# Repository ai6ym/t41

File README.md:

# T41-EP SDT Project Files

Hardware and software files for the T41-EP SDT as sold / distributed by [AI6YM](https://ai6ym.radio/t41-ep-sdt). These files are branched from [K9HZ's Repo](https://github.com/DRWJSCHMIDT/T41) and [G0ORX's Repo](https://github.com/g0orx/T41-EP) with some files from the [SoftwareControlledHamRadio Groups.IO](https://groups.io/g/SoftwareControlledHamRadio).

Changes present here are minor modifications made to enable automated SMD assembly, pre-programming of the Teensy and ATTiny, etc. Refinements to various BOMs (bill of materials) have been made to substitute parts which are unavailable or correct errors.

Software within this repository is licensed under GNU GPL v3. Hardware designs are licensed under TAPR OHL Version 1.0. In addition to these licenses the original creators of the T41, Albert F Peter (AC8GY) and Dr. Jack Purdum (W8TEE), have requested that any commercial use of the designs receive their written permission.

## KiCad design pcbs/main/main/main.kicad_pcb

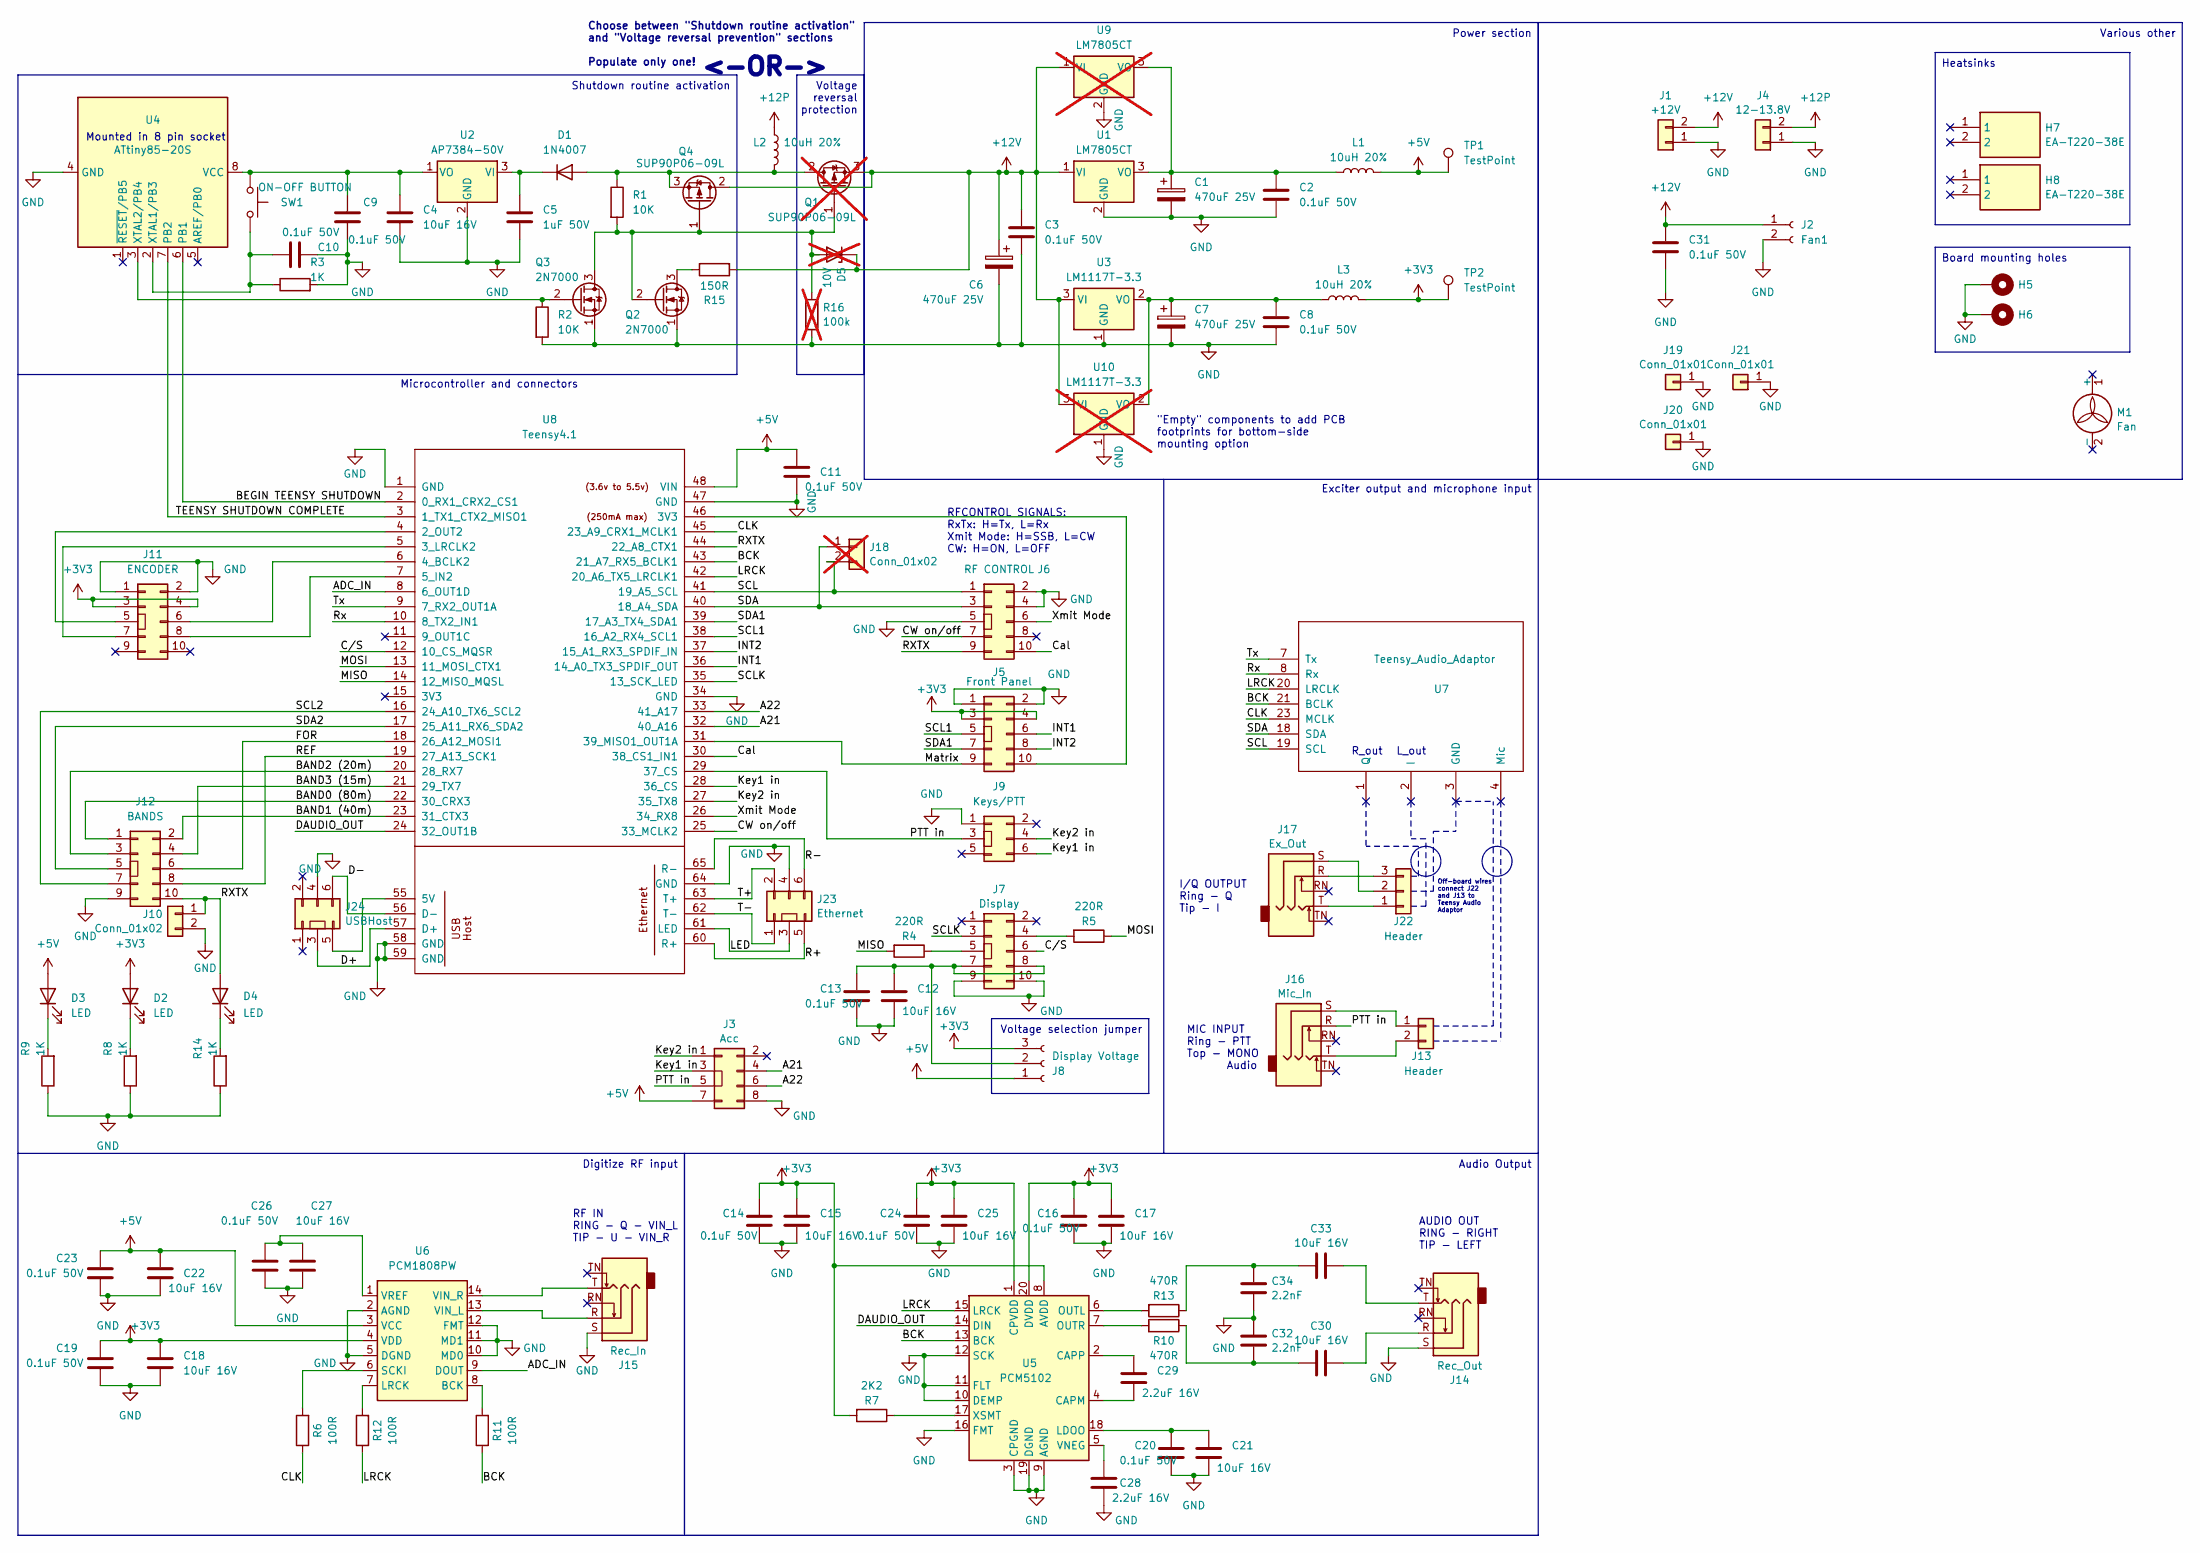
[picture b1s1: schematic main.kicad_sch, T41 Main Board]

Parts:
C1, C6, C7: 470uF 25V; CP_Radial_D10.0mm_P5.00mm; Mouser 667-ECA-1EM471
C2, C3, C8, C9, C10, C11, C13, C14, C16, C19, C20, C23, C24, C26, C31: 0.1uF 50V; C_1206_3216Metric; Mouser C1206C104K5RACTU
C4, C12, C15, C17, C18, C21, C22, C25, C27, C30, C33: 10uF 16V; C_1206_3216Metric; Mouser 80-C1206C106K4P
C5: 1uF 50V; C_1206_3216Metric; Mouser 187-CL31B105KBHNNNE
C28, C29: 2.2uF 16V; C_1206_3216Metric; Mouser 80-C1206C225K5R
C32, C34: 2.2nF; C_1206_3216Metric; Mouser 80-C1206C222K5RAC
D1: 1N4007; D_SMA; Mouser 621-S1A-F
D2, D3, D4: LED; D_1206_3216Metric; Mouser 645-599-0220-007F
D5: 10V; D_SMA; Mouser 78-MMSZ5240C-E3-08; not fitted
H5, H6: MountingHole_4.3mm_M4_DIN965_Pad
H7, H8: EA-T220-38E; EAT22038E; Mouser Part Number 588-EA-T220-38E
J1: +12V; PinHeader_1x02_P5.08mm_Vertical
J2: Fan1; PinHeader_1x02_P2.54mm_Vertical
J3: Acc; IDC-Header_2x04_P2.54mm_Vertical
J4: 12-13.8V; PinHeader_1x02_P5.08mm_Vertical
J5: Front Panel; IDC-Header_2x05_P2.54mm_Vertical
J6: RF CONTROL; IDC-Header_2x05_P2.54mm_Vertical
J7: Display; IDC-Header_2x05_P2.54mm_Vertical
J8: Display Voltage; PinHeader_1x03_P2.54mm_Vertical
J9: Keys/PTT; IDC-Header_2x03_P2.54mm_Vertical
J10: Conn_01x02; PinHeader_1x02_P2.54mm_Vertical
J11: ENCODER; IDC-Header_2x05_P2.54mm_Vertical
J12: BANDS; IDC-Header_2x05_P2.54mm_Vertical
J13: Header; PinHeader_1x02_P2.54mm_Vertical
J14: Rec_Out; Jack_3.5mm_STX-3081_Horizontal; Mouser 490-SJ1-3515N
J15: Rec_In; Jack_3.5mm_STX-3081_Horizontal; Mouser 490-SJ1-3515N
J16: Mic_In; Jack_3.5mm_STX-3081_Horizontal; Mouser 490-SJ1-3515N
J17: Ex_Out; Jack_3.5mm_STX-3081_Horizontal; Mouser 490-SJ1-3515N
J18: Conn_01x02; PinHeader_1x02_P2.54mm_Vertical; not fitted
J19, J20, J21: Conn_01x01; PinHeader_1x01_P2.54mm_Vertical
J22: Header; PinHeader_1x03_P2.54mm_Vertical
J23: Ethernet; IDC-Header_2x03_P2.54mm_Vertical; Mouser 710-61200621621
J24: USBHost; IDC-Header_2x03_P2.54mm_Vertical; Mouser 710-61200621621
L1, L2, L3: 10uH 20%; L_Bourns-SRN6028; Mouser 81-1264EY-100MP3
M1: Fan; Mouser 664-AD0412HXK96XT1
Q1: SUP90P06-09L; TO-220-3_Vertical; not fitted
Q2, Q3: 2N7000; TO-92_Inline; Mouser 512-2N7000BU
Q4: SUP90P06-09L; TO-220-3_Vertical
R1, R2: 10K; R_1206_3216Metric; Mouser CRCW120610K0FKEB
R3, R8, R9, R14: 1K; R_1206_3216Metric; Mouser CRCW12061K00JNEAC
R4, R5: 220R; R_1206_3216Metric; Mouser 279-CRGCQ1206J220R
R6, R11, R12: 100R; R_1206_3216Metric; Mouser 652-CR1206FX-1000ELF
R7: 2K2; R_1206_3216Metric; Mouser CRCW12062K20JNEAC
R10, R13: 470R; R_1206_3216Metric; Mouser CRCW1206470RJNEAC
R15: 150R; R_1206_3216Metric; Mouser 279-CRGCQ1206J150R
R16: 100k; R_1206_3216Metric; Mouser 71-CRCW1206100KFKEB; not fitted
SW1: ON-OFF BUTTON; PinHeader_1x02_P2.54mm_Vertical
TP1, TP2: TestPoint; PinHeader_1x01_P2.54mm_Vertical
U1: LM7805CT; TO-220-3_Vertical; Mouser 926-LM7805CT/NOPB
U2: AP7384-50V; TO-92_Inline_Wide; Mouser AP7381-50V-A
U3: LM1117T-3.3; TO-220-3_Vertical; Mouser 926-LM1117T-3.3/NOPB
U4: ATtiny85-20S; DIP-8_W7.62mm_Socket; Mouser 556-ATTINY85-20PU
U5: PCM5102; TSSOP-20_4.4x6.5mm_P0.65mm; Mouser 595-PCM5102APWR
U6: PCM1808PW; TSSOP-14_4.4x5mm_P0.65mm; Mouser 595-PCM1808PW
U7: Teensy_Audio_Adaptor
U8: Teensy4.1; Teensy41
U9: LM7805CT; TO-220-3_Vertical; Mouser 926-LM7805CT/NOPB; not fitted
U10: LM1117T-3.3; TO-220-3_Vertical; Mouser 926-LM1117T-3.3/NOPB; not fitted

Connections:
+3V3: C14.1, C15.1, C16.1, C17.1, C18.1, C19.1, C24.1, C25.1, D2.2 (A), J5.3, J5.4, J8.3, J11.3, J11.4, L3.2, R7.2, TP2.1, U5.1 (CPVDD), U5.8 (AVDD), U5.20 (DVDD), U6.4 (VDD)
+5V: C11.1, C22.1, C23.1, D3.2 (A), J3.7, J8.1, L1.2, TP1.1, U6.3 (VCC), U8.48 (VIN)
+12P: J4.2, L2.2
+12V: C3.1, C6.1, C31.1, D5.1 (K), J1.2, J2.1, Q1.3 (S), Q4.2 (D), R15.2, U1.1 (VI), U3.3 (VI), U9.1 (VI), U10.3 (VI)
/A21: J3.4, U8.32 (40_A16)
/A22: J3.6, U8.33 (41_A17)
/ADC_IN: U6.9 (DOUT), U8.8 (6_OUT1D)
/BAND0 (80m): J12.1, U8.22 (30_CRX3)
/BAND1 (40m): J12.2, U8.23 (31_CTX3)
/BAND2 (20m): J12.3, U8.20 (28_RX7)
/BAND3 (15m): J12.4, U8.21 (29_TX7)
/BCK: R11.1, U5.13 (BCK), U7.21 (BCLK), U8.43 (21_A7_RX5_BCLK1)
/BEGIN TEENSY SHUTDOWN: U4.6 (PB1), U8.2 (0_RX1_CRX2_CS1)
/CLK: R6.1, U7.23 (MCLK), U8.45 (23_A9_CRX1_MCLK1)
/CW on/off: J6.7, U8.25 (33_MCLK2)
/Cal: J6.10, U8.30 (38_CS1_IN1)
/C/S: J7.6, U8.12 (10_CS_MQSR)
/D+: J24.3, U8.57 (D+)
/D-: J24.6, U8.56 (D-)
/DAUDIO_OUT: U5.14 (DIN), U8.24 (32_OUT1B)
/FOR: J12.6, U8.18 (26_A12_MOSI1)
/INT1: J5.6, U8.36 (14_A0_TX3_SPDIF_OUT)
/INT2: J5.8, U8.37 (15_A1_RX3_SPDIF_IN)
/Key1 in: J3.3, J9.6, U8.28 (36_CS)
/Key2 in: J3.1, J9.4, U8.27 (35_TX8)
/LED: J23.3, U8.61 (LED)
/LRCK: R12.1, U5.15 (LRCK), U7.20 (LRCLK), U8.42 (20_A6_TX5_LRCLK1)
/MISO: R4.2, U8.14 (12_MISO_MQSL)
/MOSI: R5.1, U8.13 (11_MOSI_CTX1)
/Matrix: J5.9, U8.31 (39_MISO1_OUT1A)
/PTT in: J3.5, J9.3, J16.R, U8.29 (37_CS)
/R+: J23.5, U8.60 (R+)
/R-: J23.6, U8.65 (R-)
/REF: J12.8, U8.19 (27_A13_SCK1)
/RXTX: D4.2 (A), J6.9, J10.1, J12.10, U8.44 (22_A8_CTX1)
/Rx: U7.8 (Rx), U8.10 (8_TX2_IN1)
/SCL: J6.1, J18.2, U7.19 (SCL), U8.41 (19_A5_SCL)
/SCL1: J5.5, U8.38 (16_A2_RX4_SCL1)
/SCL2: J12.7, U8.16 (24_A10_TX6_SCL2)
/SCLK: J7.3, U8.35 (13_SCK_LED)
/SDA: J6.3, J18.1, U7.18 (SDA), U8.40 (18_A4_SDA)
/SDA1: J5.7, U8.39 (17_A3_TX4_SDA1)
/SDA2: J12.5, U8.17 (25_A11_RX6_SDA2)
/T+: J23.2, U8.63 (T+)
/T-: J23.1, U8.62 (T-)
/TEENSY SHUTDOWN COMPLETE: U4.7 (PB2), U8.3 (1_TX1_CTX2_MISO1)
/Tx: U7.7 (Tx), U8.9 (7_RX2_OUT1A)
/Xmit Mode: J6.6, U8.26 (34_RX8)
GND: C1.2, C2.2, C3.2, C4.2, C5.2, C6.2, C7.2, C8.2, C9.2, C10.2, C11.2, C12.2, C13.2, C14.2, C15.2, C16.2, C17.2, C18.2, C19.2, C20.2, C21.2, C22.2, C23.2, C24.2, C25.2, C26.2, C27.2, C28.2, C31.2, C32.1, C34.2, H5.1, H6.1, J1.1, J2.2, J3.8, J4.1, J5.1, J5.2, J6.2, J6.4, J6.5, J7.9, J7.10, J9.1, J10.2, J11.1, J11.2, J12.9, J14.S, J15.S, J19.1, J20.1, J21.1, J23.4, J24.4, Q2.1 (S), Q3.1 (S), R2.2, R3.2, R8.1, R9.1, R14.1, R16.2, U1.2 (GND), U2.2 (GND), U3.1 (GND), U4.4 (GND), U5.3 (CPGND), U5.9 (AGND), U5.10 (DEMP), U5.11 (FLT), U5.12 (SCK), U5.16 (FMT), U5.19 (DGND), U6.2 (AGND), U6.5 (DGND), U6.10 (MD0), U6.11 (MD1), U6.12 (FMT), U8.1 (GND), U8.34 (GND), U8.47 (GND), U8.58 (GND), U8.59 (GND), U8.64 (GND), U9.2 (GND), U10.1 (GND)
unnamed: C30.1, C32.2, R10.1
unnamed: C30.2, J14.R
unnamed: C33.1, C34.1, R13.1
unnamed: C33.2, J14.T
unnamed: D1.2 (A), L2.1, Q1.2 (D), Q4.3 (S), R1.1
unnamed: C5.1, D1.1 (K), U2.3 (VI)
unnamed: D2.1 (K), R8.2
unnamed: D3.1 (K), R9.2
unnamed: D4.1 (K), R14.2
unnamed: D5.2 (A), Q1.1 (G), Q2.2 (G), Q3.3 (D), Q4.1 (G), R1.2, R16.1
unnamed: J5.10, U8.46 (3V3)
unnamed: J7.4, R5.2
unnamed: J7.5, R4.1
unnamed: C12.1, C13.1, J7.7, J7.8, J8.2
unnamed: J11.5, U8.4 (2_OUT2)
unnamed: J11.6, U8.6 (4_BCLK2)
unnamed: J11.7, U8.5 (3_LRCLK2)
unnamed: J11.8, U8.7 (5_IN2)
unnamed: J13.1, J16.S
unnamed: J13.2, J16.T
unnamed: J17.T, J22.1
unnamed: J17.S, J22.2
unnamed: J17.R, J22.3
unnamed: J24.5, U8.55 (5V)
unnamed: Q2.3 (D), R15.1
unnamed: Q3.2 (G), R2.1, U4.3 (XTAL2/PB4)
unnamed: C1.1, C2.1, L1.1, U1.3 (VO), U9.3 (VO)
unnamed: C4.1, C9.1, SW1.1, U2.1 (VO), U4.8 (VCC)
unnamed: C10.1, R3.1, SW1.2, U4.2 (XTAL1/PB3)
unnamed: C29.2, U5.4 (CAPM)
unnamed: C29.1, U5.2 (CAPP)
unnamed: C20.1, C21.1, U5.18 (LDOO)
unnamed: R13.2, U5.6 (OUTL)
unnamed: R10.2, U5.7 (OUTR)
unnamed: C28.1, U5.5 (VNEG)
unnamed: R7.1, U5.17 (XSMT)
unnamed: R11.2, U6.8 (BCK)
unnamed: R12.2, U6.7 (LRCK)
unnamed: R6.2, U6.6 (SCKI)
unnamed: J15.R, U6.13 (VIN_L)
unnamed: J15.T, U6.14 (VIN_R)
unnamed: C26.1, C27.1, U6.1 (VREF)
unnamed: C7.1, C8.1, L3.1, U3.2 (VO), U10.2 (VO)

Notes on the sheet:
Various other
Voltage selection jumper
Heatsinks
Power section
Digitize RF input
Audio Output
Shutdown routine activation
Voltage reversal protection
Board mounting holes
Mounted in 8 pin socket
MIC INPUT Ring - PTT Top - MONO Audio
<-OR->
RF IN RING - Q - VIN_L TIP - U - VIN_R
I/Q OUTPUT Ring - Q Tip - I
AUDIO OUT RING - RIGHT TIP - LEFT
L_out
Microcontroller and connectors
"Empty" components to add PCB footprints for bottom-side mounting option
Off-board wires connect J22 and J13 to Teensy Audio Adaptor
Choose between "Shutdown routine activation" and "Voltage reversal prevention" sections Populate only one!
RFCONTROL SIGNALS: RxTx: H=Tx, L=Rx Xmit Mode: H=SSB, L=CW CW: H=ON, L=OFF
Exciter output and microphone input
R_out

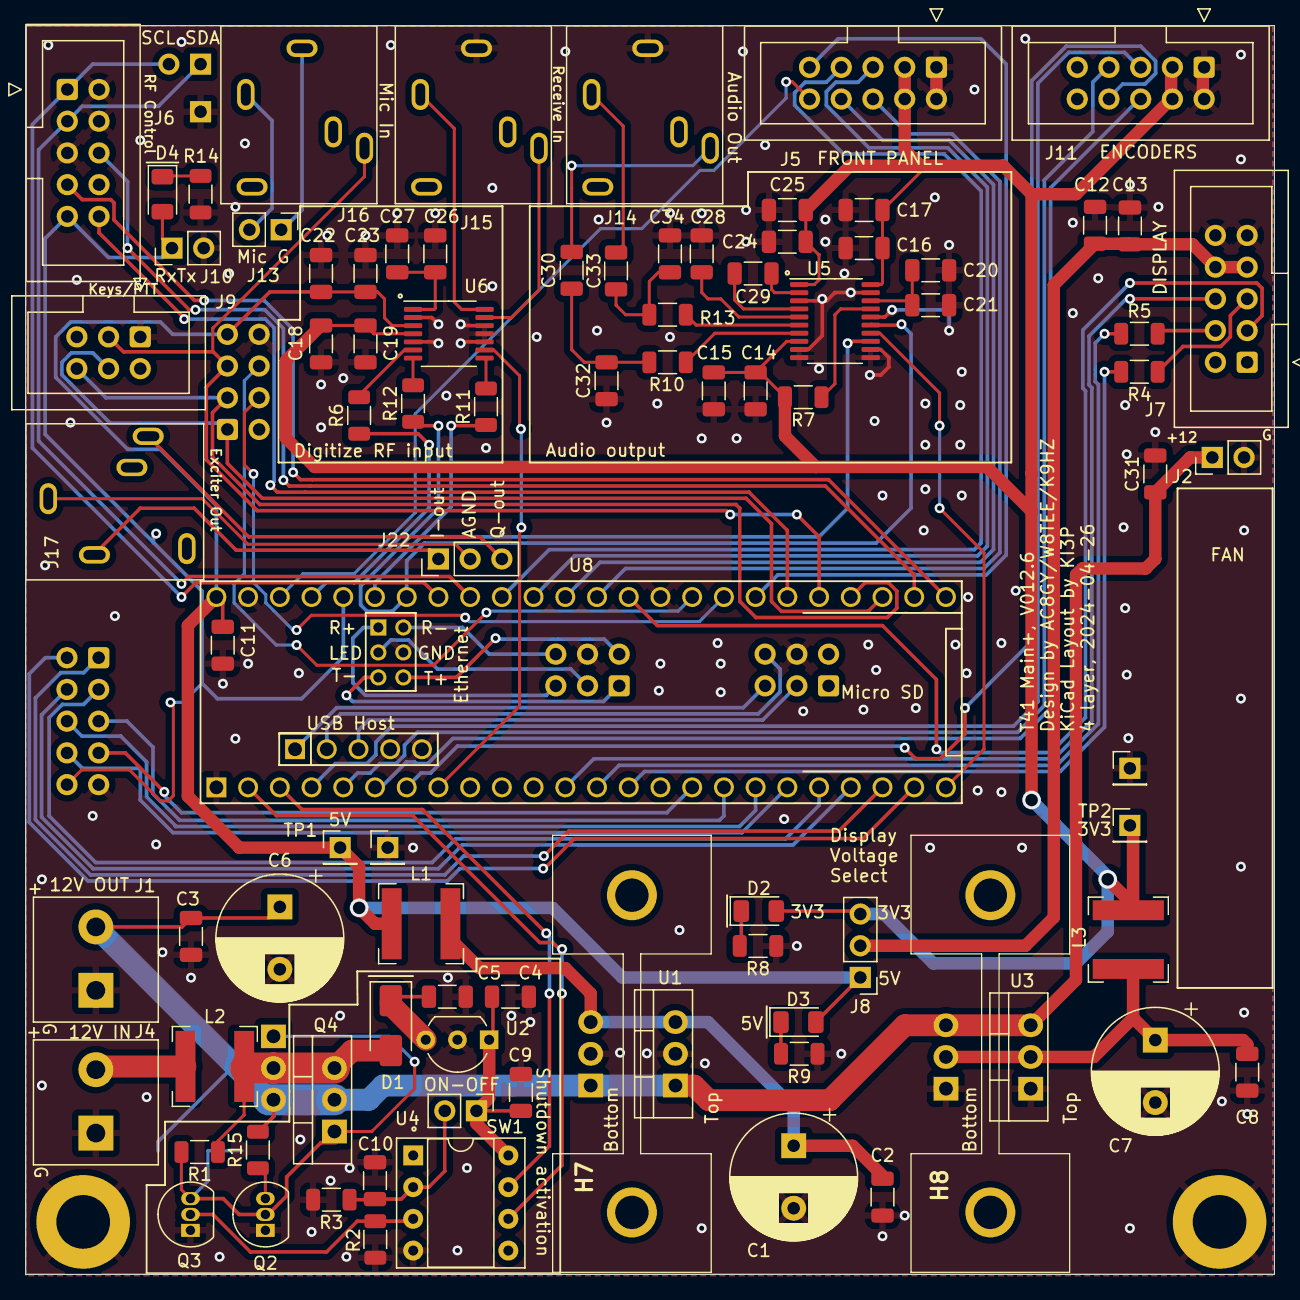
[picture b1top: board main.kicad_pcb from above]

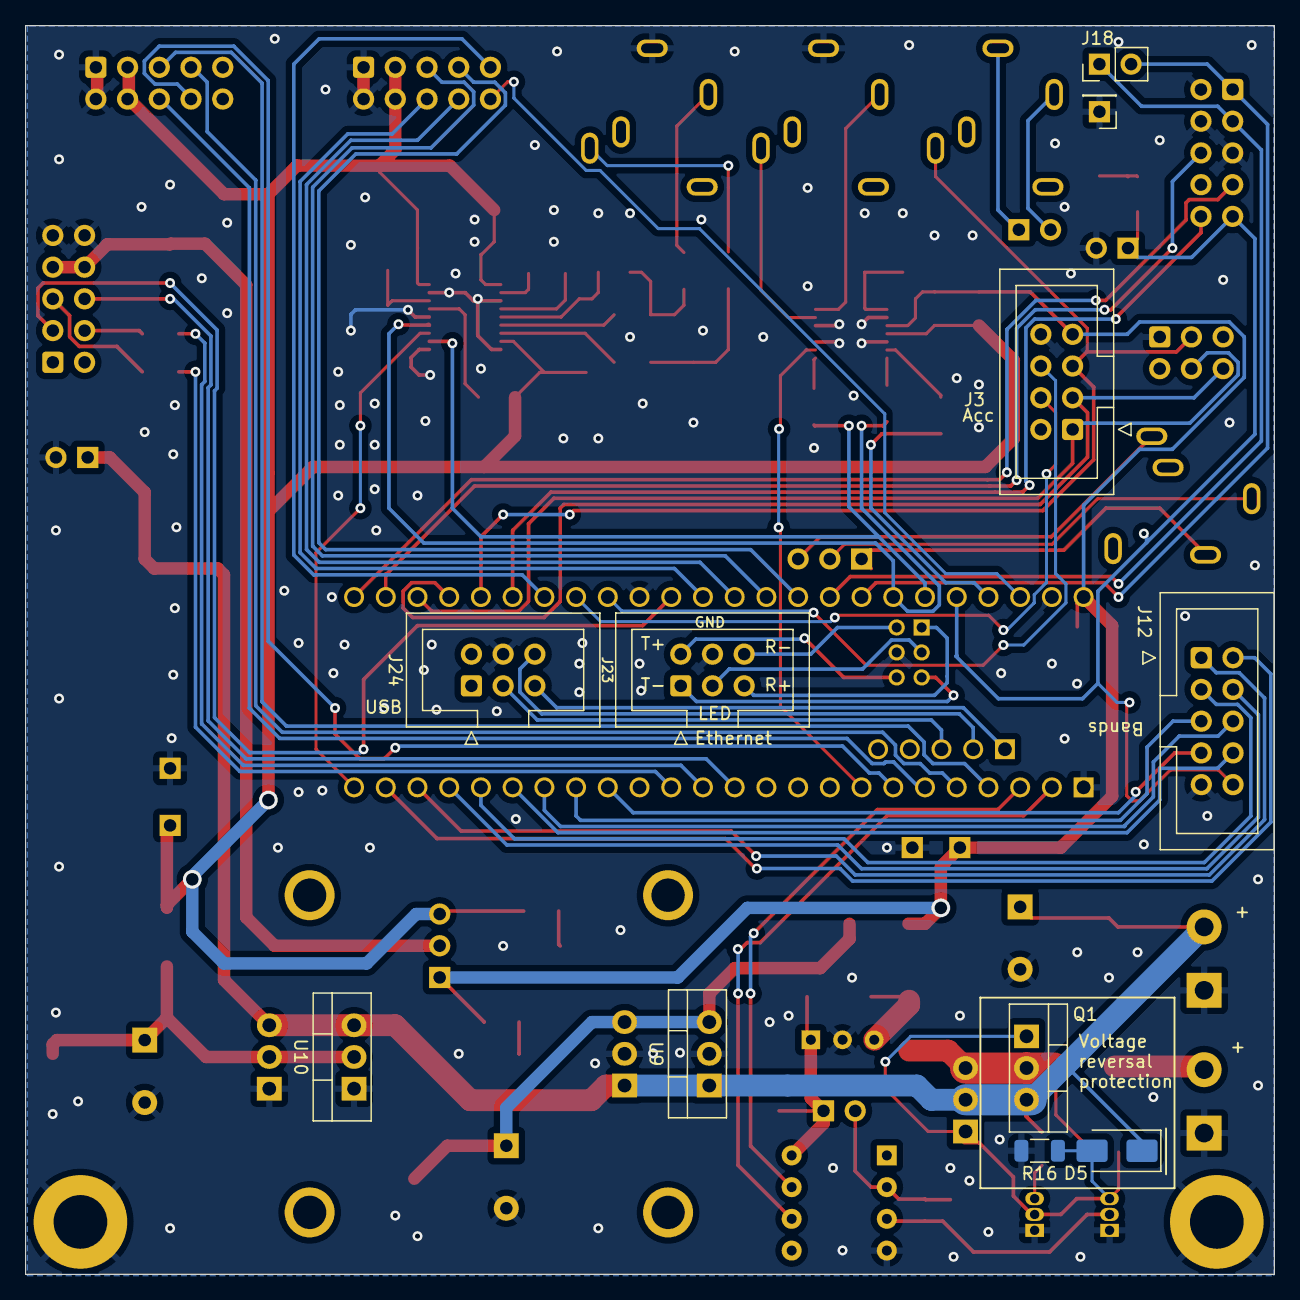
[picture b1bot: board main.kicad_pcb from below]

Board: 4 copper layers, 100.0 x 100.0 mm, 102 parts (11 on the bottom side), 90 nets.

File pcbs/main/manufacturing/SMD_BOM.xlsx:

|  |  | xxxx xxxx xxxxx xxPCS BOM (Sample Bill of Materials)
Item # | *Designator | *Qty | Manufacturer | *Mfg Part # | Description / Value | *Package/Footprint | Type | Your Instructions / Notes
1 | C2, C3, C8, C9, C10, C11, C13, C14, C16, C19, C20, C23, C24, C26, C31 | 15 | KEMET | C1206C104K5RACTU | 0.1uF 50V SMD 1206 Ceramic Capacitor | 1206 | SMD
2 | C32, C34 | 2 | KEMET | C1206C222K5RAC | 2.2nF 50V SMD 1206 Capacitor | 1206 | SMD
3 | C28, C29 | 2 | KEMET | C1206C225K5R | 2.2uF 25V SMD 1206 Capacitor | 1206 | SMD
4 | C4, C12, C15, C17, C18, C21, C22, C25, C27, C30, C33 | 11 | KEMET | C1206C106K4P | 10uF 16V SMD 1206 Capacitor | 1206 | SMD
5 | D2, D3, D4 | 3 | Dialight | 599-0220-007F | LED Diodes SMD; Colors to suit | 1206 | SMD
6 | L1, L2, L3 | 3 | Murata Electronics | 1264EY-100M=P3 | Inductor 10uH 20% | 2424 | SMD
7 | R6, R11, R12 | 3 | Bourns | CR1206-FX-1000ELF | 100 Ohm SMD 1206 Resistor | 1206 | SMD
8 | R15 | 1 | YAGEO | RC1206JR-07150RL | 150 Ohm SMD 1206 Resistor | 1206 | SMD
9 | R4, R5 | 2 | TE Connectivity / Holsworthy | CRGCQ1206J220R | 220 Ohm SMD 1206 Resistor | 1206 | SMD
10 | R8, R9, R14 | 3 | SEI Stackpole | RMCF1206FT330R | 330 Ohm SMD 1206 Resistor | 1206 | SMD
11 | R10, R13 | 2 | Vishay / Dale | CRCW1206470RJNEAC | 470 Ohm SMD 1206 Resistor | 1206 | SMD
12 | R7 | 1 | Vishay / Dale | CRCW12062K20JNEAC | 2.2K Ohm SMD 1206 Resistor | 1206 | SMD
13 | U5 | 1 | Texas Instruments | PCM5102APWR | PCM5102APW Stereo DAC TSSOP-20 |  | SMD
14 | U6 | 1 | Texas Instruments | PCM1808PWR | PCM1808PWR Stereo ADC TSSOP-14 |  | SMD
15 | C5 | 1 | Samsung Electro-Mechanics | CL31B105KBHNNNE | 1.0uF 50V SMD 1206 Capacitor | 1206 | SMD
16 | D1 | 1 | Diodes Incorporated | S1A-13-F | S1A-13-F Diode or equivalent (1N4001) |  | SMD
17 | R3 | 1 | Vishay / Dale | CRCW12061K00JNEAC | 1K Ohm SMD 1206 Resistor | 1206 | SMD
18 | R1, R2 | 2 | Vishay / Dale | CRCW120610K0FKEB | 10K Ohm SMD 1206 Resistor | 1206 | SMD
Need a quick and accurante quote? Need an efficient production? Please read SMT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
Click for Instructions on How to Create a BOM

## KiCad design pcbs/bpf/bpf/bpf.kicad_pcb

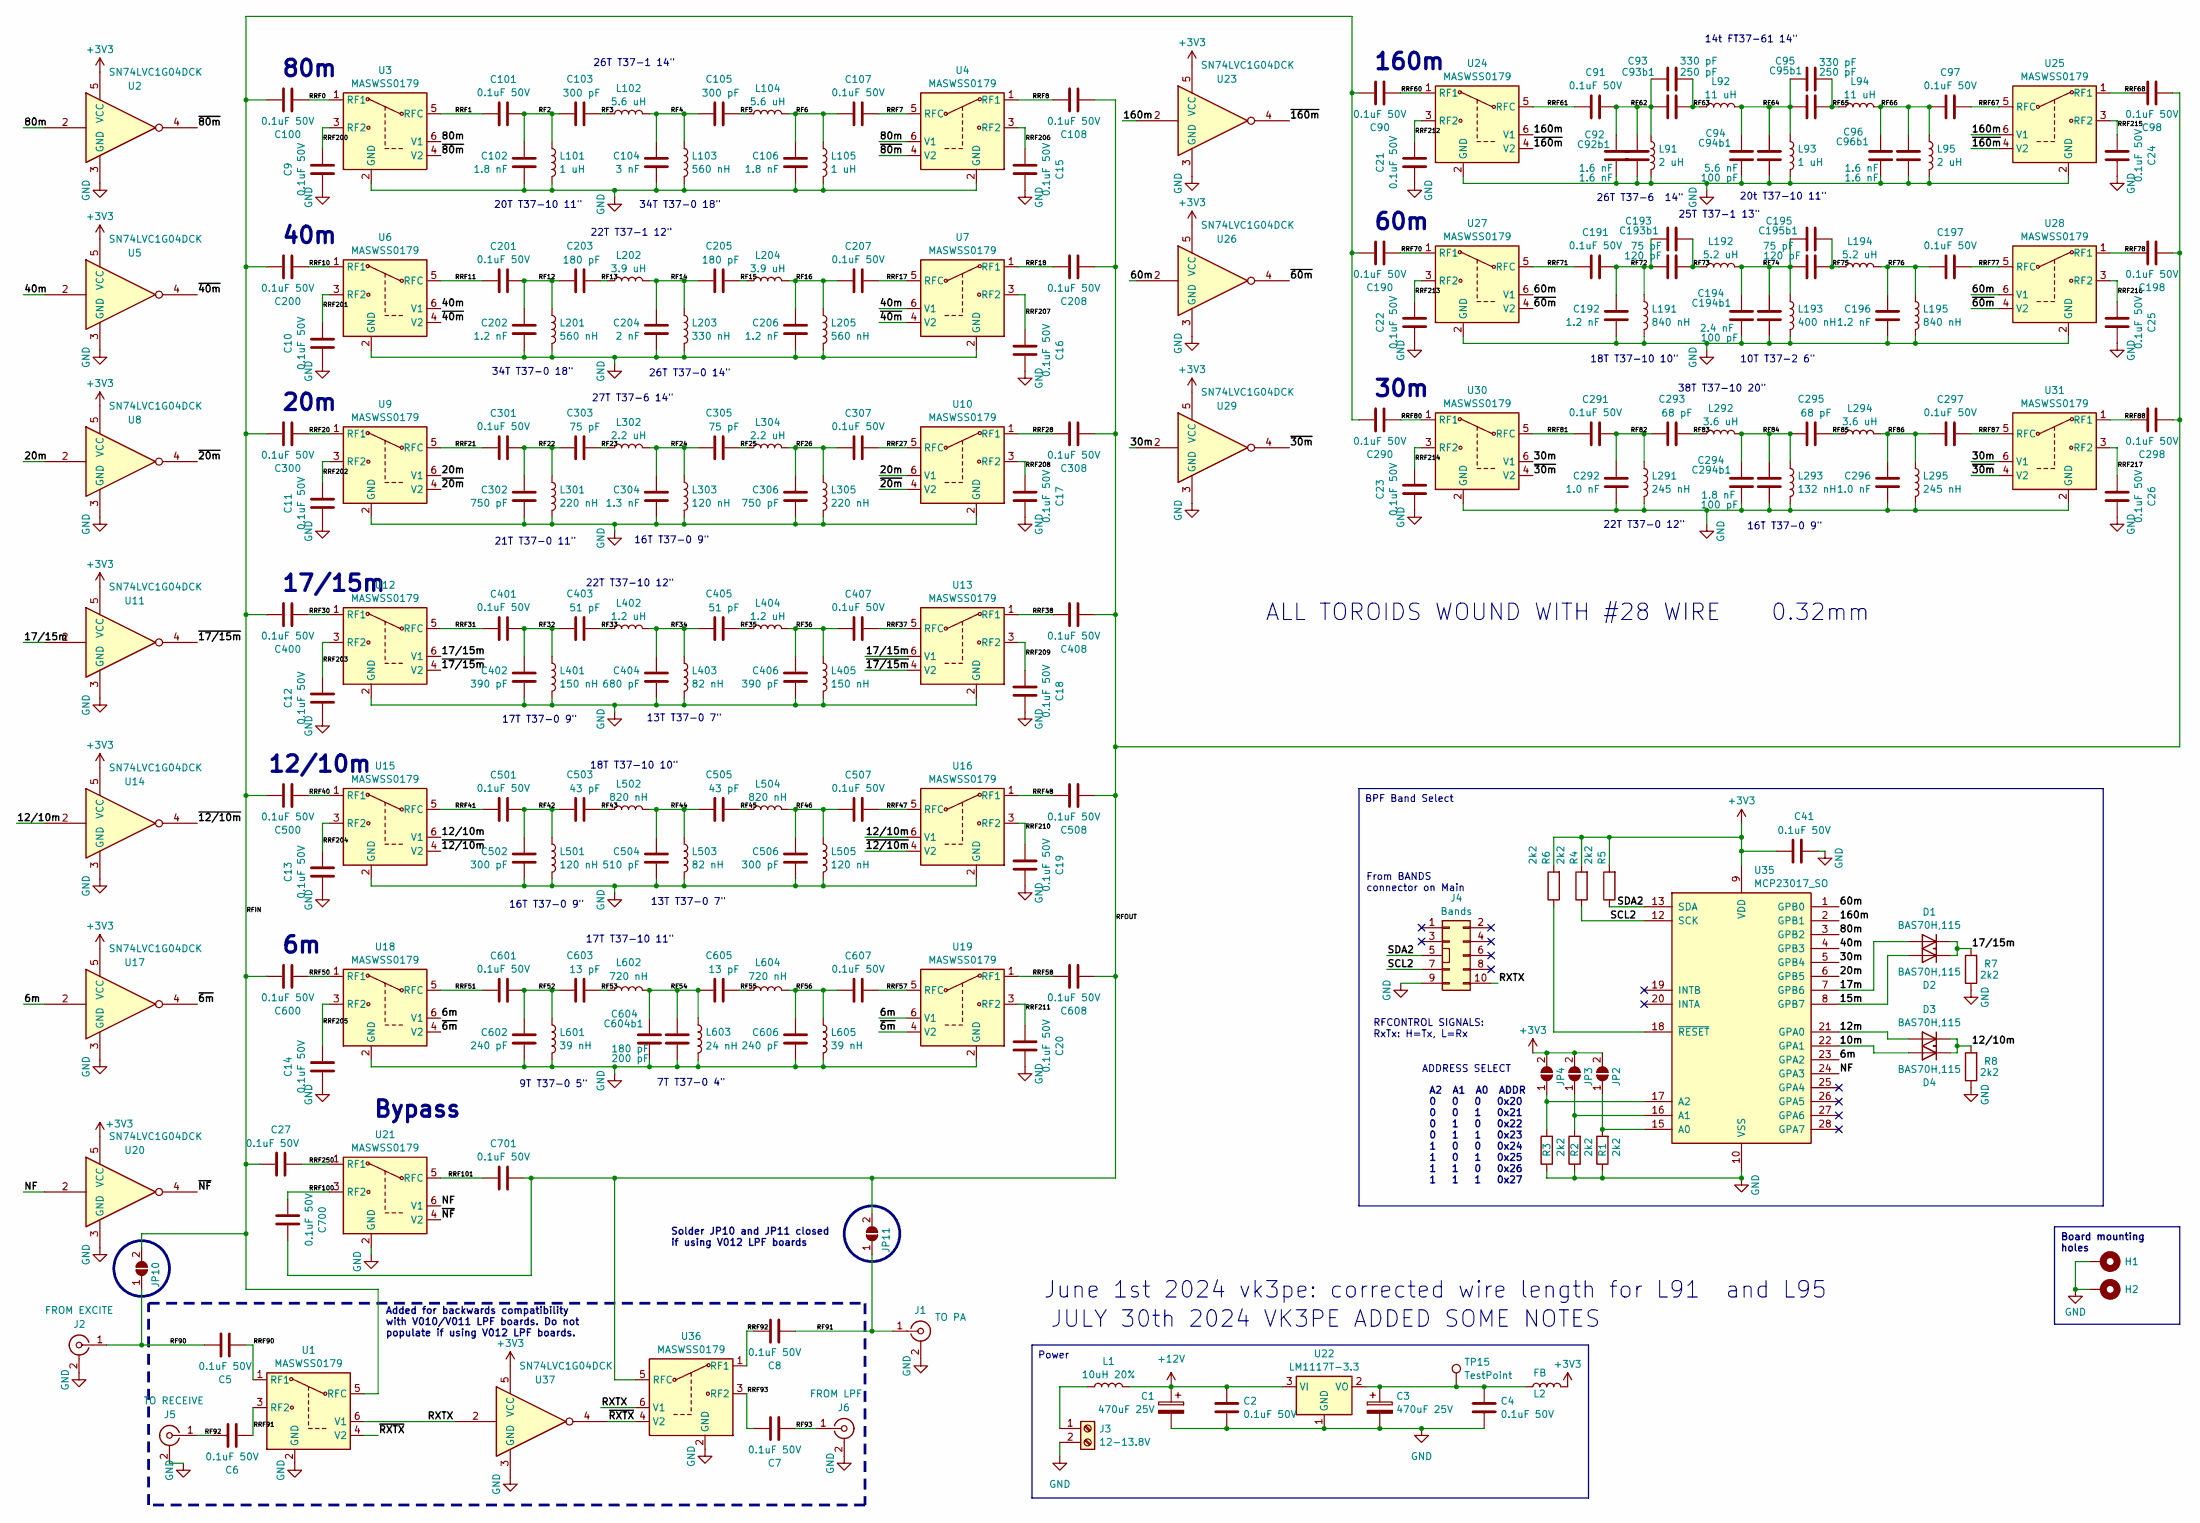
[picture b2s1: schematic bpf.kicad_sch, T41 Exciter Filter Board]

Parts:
C1, C3: 470uF 25V; CP_Radial_D10.0mm_P5.00mm; Mouser Part Number 667-ECA-1EM471
C2, C4, C5, C6, C7, C8, C9, C10, C11, C12, C13, C14, C15, C16, C17, C18, C19, C20, C21, C22, C23, C24, C25, C26, C27, C90, C91, C97, C98, C100, C101, C107, C108, C190, C191, C197, C198, C200, C201, C207, C208, C290, C291, C297, C298, C300, C301, C307, C308, C400, C401, C407, C408, C500, C501, C507, C508, C600, C601, C607, C608, C700, C701: 0.1uF 50V; C_1206_3216Metric; Mouser Part Number C1206C104K5RACTU
C41: 0.1uF 50V; C_1206_3216Metric; Mouser Part Number 581-12065F104K4
C92, C92b1, C96, C96b1: 1.6 nF; C_1206_3216Metric
C93, C95: 330 pF; C_1206_3216Metric
C93b1, C95b1: 250 pF; C_1206_3216Metric
C94: 5.6 nF; C_1206_3216Metric
C94b1, C194b1, C294b1: 100 pF; C_1206_3216Metric
C102, C106, C294: 1.8 nF; C_1206_3216Metric
C103, C105, C502, C506: 300 pF; C_1206_3216Metric
C104: 3 nF; C_1206_3216Metric
C192, C196, C202, C206: 1.2 nF; C_1206_3216Metric
C193, C195, C303, C305: 75 pF; C_1206_3216Metric
C193b1, C195b1: 120 pF; C_1206_3216Metric
C194: 2.4 nF; C_1206_3216Metric
C203, C205, C604: 180 pF; C_1206_3216Metric
C204: 2 nF; C_1206_3216Metric
C292, C296: 1.0 nF; C_1206_3216Metric
C293, C295: 68 pF; C_1206_3216Metric
C302, C306: 750 pF; C_1206_3216Metric
C304: 1.3 nF; C_1206_3216Metric
C402, C406: 390 pF; C_1206_3216Metric
C403, C405: 51 pF; C_1206_3216Metric
C404: 680 pF; C_1206_3216Metric
C503, C505: 43 pF; C_1206_3216Metric
C504: 510 pF; C_1206_3216Metric
C602, C606: 240 pF; C_1206_3216Metric
C603, C605: 13 pF; C_1206_3216Metric
C604b1: 200 pF; C_1206_3216Metric
D1, D2, D3, D4: BAS70H,115; D_SOD-123F; Mouser Part Number 771-BAS70H-T/R
H1, H2: MountingHole_4.3mm_M4_DIN965_Pad
J1: TO PA; SMA_Amphenol_901-144_Vertical; Mouser Part Number 712-CONSMA001-G
J2: FROM EXCITE; SMA_Amphenol_901-144_Vertical; Mouser Part Number 712-CONSMA001-G
J3: 12-13.8V; TerminalBlock_bornier-2_P5.08mm; Mouser Part Number 538-39880-4302
J4: Bands; IDC-Header_2x05_P2.54mm_Vertical
J5: TO RECEIVE; SMA_Amphenol_901-144_Vertical; Mouser Part Number 712-CONSMA001-G
J6: FROM LPF; SMA_Amphenol_901-144_Vertical; Mouser Part Number 712-CONSMA001-G
JP2, JP3, JP4, JP10, JP11: SolderJumper_2_Open; SolderJumper-2_P1.3mm_Open_TrianglePad1.0x1.5mm
L1: 10uH 20%; L_Bourns-SRN6028; Mouser Part Number 81-1264EY-100MP3
L2: FB; R_1206_3216Metric; Mouser Part Number 875-HZ1206E601R-10
L91, L95: 2 uH; FT37-toroid-vertical
L92, L94: 11 uH; FT37-toroid-vertical
L93, L101, L105: 1 uH; FT37-toroid-vertical
L102, L104: 5.6 uH; FT37-toroid-vertical
L103, L201, L205: 560 nH; FT37-toroid-vertical
L191, L195: 840 nH; FT37-toroid-vertical
L192, L194: 5.2 uH; FT37-toroid-vertical
L193: 400 nH; FT37-toroid-vertical
L202, L204: 3.9 uH; FT37-toroid-vertical
L203: 330 nH; FT37-toroid-vertical
L291, L295: 245 nH; FT37-toroid-vertical
L292, L294: 3.6 uH; FT37-toroid-vertical
L293: 132 nH; FT37-toroid-vertical
L301, L305: 220 nH; FT37-toroid-vertical
L302, L304: 2.2 uH; FT37-toroid-vertical
L303, L501, L505: 120 nH; FT37-toroid-vertical
L401, L405: 150 nH; FT37-toroid-vertical
L402, L404: 1.2 uH; FT37-toroid-vertical
L403, L503: 82 nH; FT37-toroid-vertical
L502, L504: 820 nH; FT37-toroid-vertical
L601, L605: 39 nH; FT37-toroid-vertical
L602, L604: 720 nH; FT37-toroid-vertical
L603: 24 nH; FT37-toroid-vertical
R1, R2, R3, R4, R5, R6, R7, R8: 2k2; R_1206_3216Metric; Mouser Part Number 652-CR1206FX-2201ELF
TP15: TestPoint; PinHeader_1x01_P2.54mm_Vertical
U1, U3, U4, U6, U7, U9, U10, U12, U13, U15, U16, U18, U19, U21, U24, U25, U27, U28, U30, U31, U36: MASWSS0179; MASWSS0179-SOT-26; Mouser Part Number 937-MASWSS0179-T
U2, U5, U8, U11, U14, U17, U20, U23, U26, U29, U37: SN74LVC1G04DCK; SOT-SC70; Mouser Part Number 595-SN74LVC1G04DCKR
U22: LM1117T-3.3; TO-220-3_Vertical; Mouser Part Number 926-LM1117T-3.3/NOPB
U35: MCP23017_SO; SOIC-28W_7.5x17.9mm_P1.27mm; Mouser Part Number 579-MCP23017-E/SO

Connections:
+3V3: C41.2, JP2.2 (B), JP3.2 (B), JP4.2 (B), L2.1, R4.2, R5.2, R6.2, U2.5 (VCC), U5.5 (VCC), U8.5 (VCC), U11.5 (VCC), U14.5 (VCC), U17.5 (VCC), U20.5 (VCC), U23.5 (VCC), U26.5 (VCC), U29.5 (VCC), U35.9 (VDD), U37.5 (VCC)
+12V: C1.1, C2.1, L1.2, U22.3 (VI)
/6m: U17.2, U18.6 (V1), U19.6 (V1), U35.23 (GPA2)
/10m: D4.2 (A), U35.22 (GPA1)
/12m: D3.2 (A), U35.21 (GPA0)
/12/10m: D3.1 (K), D4.1 (K), R8.2, U14.2, U15.6 (V1), U16.6 (V1)
/15m: D2.2 (A), U35.8 (GPB7)
/17m: D1.2 (A), U35.7 (GPB6)
/17/15m: D1.1 (K), D2.1 (K), R7.2, U11.2, U12.6 (V1), U13.6 (V1)
/20m: U8.2, U9.6 (V1), U10.6 (V1), U35.6 (GPB5)
/30m: U29.2, U30.6 (V1), U31.6 (V1), U35.5 (GPB4)
/40m: U5.2, U6.6 (V1), U7.6 (V1), U35.4 (GPB3)
/60m: U26.2, U27.6 (V1), U28.6 (V1), U35.1 (GPB0)
/80m: U2.2, U3.6 (V1), U4.6 (V1), U35.3 (GPB2)
/160m: U23.2, U24.6 (V1), U25.6 (V1), U35.2 (GPB1)
/NF: U20.2, U21.6 (V1), U35.24 (GPA3)
/RF2: C101.2, C102.2, C103.2, L101.1
/RF3: C103.1, L102.1
/RF4: C104.2, C105.2, L102.2, L103.1
/RF5: C105.1, L104.1
/RF6: C106.2, C107.1, L104.2, L105.1
/RF12: C201.2, C202.2, C203.2, L201.1
/RF13: C203.1, L202.1
/RF14: C204.2, C205.2, L202.2, L203.1
/RF15: C205.1, L204.1
/RF16: C206.2, C207.1, L204.2, L205.1
/RF22: C301.2, C302.2, C303.2, L301.1
/RF23: C303.1, L302.1
/RF24: C304.2, C305.2, L302.2, L303.1
/RF25: C305.1, L304.1
/RF26: C306.2, C307.1, L304.2, L305.1
/RF32: C401.2, C402.2, C403.2, L401.1
/RF33: C403.1, L402.1
/RF34: C404.2, C405.2, L402.2, L403.1
/RF35: C405.1, L404.1
/RF36: C406.2, C407.1, L404.2, L405.1
/RF42: C501.2, C502.2, C503.2, L501.1
/RF43: C503.1, L502.1
/RF44: C504.2, C505.2, L502.2, L503.1
/RF45: C505.1, L504.1
/RF46: C506.2, C507.1, L504.2, L505.1
/RF52: C601.2, C602.2, C603.2, L601.1
/RF53: C603.1, L602.1
/RF54: C604.2, C604b1.2, C605.2, L602.2, L603.1
/RF55: C605.1, L604.1
/RF56: C606.2, C607.1, L604.2, L605.1
/RF62: C91.2, C92.2, C92b1.2, C93.2, C93b1.2, L91.1
/RF63: C93.1, C93b1.1, L92.1
/RF64: C94.2, C94b1.2, C95.2, C95b1.2, L92.2, L93.1
/RF65: C95.1, C95b1.1, L94.1
/RF66: C96.2, C96b1.2, C97.1, L94.2, L95.1
/RF72: C191.2, C192.2, C193.2, C193b1.2, L191.1
/RF73: C193.1, C193b1.1, L192.1
/RF74: C194.2, C194b1.2, C195.2, C195b1.2, L192.2, L193.1
/RF75: C195.1, C195b1.1, L194.1
/RF76: C196.2, C197.1, L194.2, L195.1
/RF82: C291.2, C292.2, C293.2, L291.1
/RF83: C293.1, L292.1
/RF84: C294.2, C294b1.2, C295.2, L292.2, L293.1
/RF85: C295.1, L294.1
/RF86: C296.2, C297.1, L294.2, L295.1
/RF90: C5.1, J2.1 (In), JP10.1 (A)
/RF91: C8.2, J1.1 (In), JP11.1 (A)
/RF92: C6.1, J5.1 (In)
/RF93: C7.2, J6.1 (In)
/RFIN: C27.2, C90.1, C100.1, C190.1, C200.1, C290.1, C300.1, C400.1, C500.1, C600.1, JP10.2 (B), U1.5 (RFC)
/RFOUT: C98.2, C108.2, C198.2, C208.2, C298.2, C308.2, C408.2, C508.2, C608.2, C700.1, C701.2, JP11.2 (B), U36.5 (RFC)
/RRF0: C100.2, U3.1 (RF1)
/RRF1: C101.1, U3.5 (RFC)
/RRF7: C107.2, U4.5 (RFC)
/RRF8: C108.1, U4.1 (RF1)
/RRF10: C200.2, U6.1 (RF1)
/RRF11: C201.1, U6.5 (RFC)
/RRF17: C207.2, U7.5 (RFC)
/RRF18: C208.1, U7.1 (RF1)
/RRF20: C300.2, U9.1 (RF1)
/RRF21: C301.1, U9.5 (RFC)
/RRF27: C307.2, U10.5 (RFC)
/RRF28: C308.1, U10.1 (RF1)
/RRF30: C400.2, U12.1 (RF1)
/RRF31: C401.1, U12.5 (RFC)
/RRF37: C407.2, U13.5 (RFC)
/RRF38: C408.1, U13.1 (RF1)
/RRF40: C500.2, U15.1 (RF1)
/RRF41: C501.1, U15.5 (RFC)
/RRF47: C507.2, U16.5 (RFC)
/RRF48: C508.1, U16.1 (RF1)
/RRF50: C600.2, U18.1 (RF1)
/RRF51: C601.1, U18.5 (RFC)
/RRF57: C607.2, U19.5 (RFC)
/RRF58: C608.1, U19.1 (RF1)
/RRF60: C90.2, U24.1 (RF1)
/RRF61: C91.1, U24.5 (RFC)
/RRF67: C97.2, U25.5 (RFC)
/RRF68: C98.1, U25.1 (RF1)
/RRF70: C190.2, U27.1 (RF1)
/RRF71: C191.1, U27.5 (RFC)
/RRF77: C197.2, U28.5 (RFC)
/RRF78: C198.1, U28.1 (RF1)
/RRF80: C290.2, U30.1 (RF1)
/RRF81: C291.1, U30.5 (RFC)
/RRF87: C297.2, U31.5 (RFC)
/RRF88: C298.1, U31.1 (RF1)
/RRF90: C5.2, U1.1 (RF1)
/RRF91: C6.2, U1.3 (RF2)
/RRF92: C8.1, U36.1 (RF1)
/RRF93: C7.1, U36.3 (RF2)
/RRF100: C700.2, U21.3 (RF2)
/RRF101: C701.1, U21.5 (RFC)
/RRF200: C9.1, U3.3 (RF2)
/RRF201: C10.1, U6.3 (RF2)
/RRF202: C11.1, U9.3 (RF2)
/RRF203: C12.1, U12.3 (RF2)
/RRF204: C13.1, U15.3 (RF2)
/RRF205: C14.1, U18.3 (RF2)
/RRF206: C15.2, U4.3 (RF2)
/RRF207: C16.2, U7.3 (RF2)
/RRF208: C17.2, U10.3 (RF2)
/RRF209: C18.2, U13.3 (RF2)
/RRF210: C19.2, U16.3 (RF2)
/RRF211: C20.2, U19.3 (RF2)
/RRF212: C21.2, U24.3 (RF2)
/RRF213: C22.2, U27.3 (RF2)
/RRF214: C23.2, U30.3 (RF2)
/RRF215: C24.2, U25.3 (RF2)
/RRF216: C25.2, U28.3 (RF2)
/RRF217: C26.2, U31.3 (RF2)
/RRF250: C27.1, U21.1 (RF1)
/RXTX: J4.10, U1.6 (V1), U36.6 (V1), U37.2
/SCL2: J4.7, R4.1, U35.12 (SCK)
/SDA2: J4.5, R5.1, U35.13 (SDA)
/~6m: U17.4, U18.4 (V2), U19.4 (V2)
/~12/10m: U14.4, U15.4 (V2), U16.4 (V2)
/~17/15m: U11.4, U12.4 (V2), U13.4 (V2)
/~20m: U8.4, U9.4 (V2), U10.4 (V2)
/~30m: U29.4, U30.4 (V2), U31.4 (V2)
/~40m: U5.4, U6.4 (V2), U7.4 (V2)
/~60m: U26.4, U27.4 (V2), U28.4 (V2)
/~80m: U2.4, U3.4 (V2), U4.4 (V2)
/~160m: U23.4, U24.4 (V2), U25.4 (V2)
/~NF: U20.4, U21.4 (V2)
/~RXTX: U1.4 (V2), U36.4 (V2), U37.4
GND: C1.2, C2.2, C3.2, C4.2, C9.2, C10.2, C11.2, C12.2, C13.2, C14.2, C15.1, C16.1, C17.1, C18.1, C19.1, C20.1, C21.1, C22.1, C23.1, C24.1, C25.1, C26.1, C41.1, C92.1, C92b1.1, C94.1, C94b1.1, C96.1, C96b1.1, C102.1, C104.1, C106.1, C192.1, C194.1, C194b1.1, C196.1, C202.1, C204.1, C206.1, C292.1, C294.1, C294b1.1, C296.1, C302.1, C304.1, C306.1, C402.1, C404.1, C406.1, C502.1, C504.1, C506.1, C602.1, C604.1, C604b1.1, C606.1, H1.1, H2.1, J1.2 (Ext), J2.2 (Ext), J3.2, J4.9, J5.2 (Ext), J6.2 (Ext), L91.2, L93.2, L95.2, L101.2, L103.2, L105.2, L191.2, L193.2, L195.2, L201.2, L203.2, L205.2, L291.2, L293.2, L295.2, L301.2, L303.2, L305.2, L401.2, L403.2, L405.2, L501.2, L503.2, L505.2, L601.2, L603.2, L605.2, R1.1, R2.1, R3.1, R7.1, R8.1, U1.2 (GND), U2.3 (GND), U3.2 (GND), U4.2 (GND), U5.3 (GND), U6.2 (GND), U7.2 (GND), U8.3 (GND), U9.2 (GND), U10.2 (GND), U11.3 (GND), U12.2 (GND), U13.2 (GND), U14.3 (GND), U15.2 (GND), U16.2 (GND), U17.3 (GND), U18.2 (GND), U19.2 (GND), U20.3 (GND), U21.2 (GND), U22.1 (GND), U23.3 (GND), U24.2 (GND), U25.2 (GND), U26.3 (GND), U27.2 (GND), U28.2 (GND), U29.3 (GND), U30.2 (GND), U31.2 (GND), U35.10 (VSS), U36.2 (GND), U37.3 (GND)
unnamed: J3.1, L1.1
unnamed: JP2.1 (A), R1.2, U35.15 (A0)
unnamed: JP3.1 (A), R2.2, U35.16 (A1)
unnamed: JP4.1 (A), R3.2, U35.17 (A2)
unnamed: C3.1, C4.1, L2.2, TP15.1, U22.2 (VO)
unnamed: R6.1, U35.18 (~RESET)

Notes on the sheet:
BPF Band Select
Power
Board mounting holes
16T T37-0 9"
22T T37-1 12"
34T T37-0 18"
18T T37-10 10"
20m
June 1st 2024 vk3pe: corrected wire length for L91 and L95
Added for backwards compatibility with V010/V011 LPF boards. Do not populate if using V012 LPF boards.
22T T37-10 12"
22T T37-0 12"
26T T37-6 14"
17T T37-0 9"
9T T37-0 5"
16T T37-0 9"
14t FT37-61 14"
ALL TOROIDS WOUND WITH #28 WIRE 0.32mm
27T T37-6 14"
38T T37-10 20"
26T T37-0 14"
13T T37-0 7"
12/10m
17T T37-10 11"
A2 A1 A0 ADDR 0 0 0 0x20 0 0 1 0x21 0 1 0 0x22 0 1 1 0x23 1 0 0 0x24 1 0 1 0x25 1 1 0 0x26 1 1 1 0x27
RFCONTROL SIGNALS: RxTx: H=Tx, L=Rx
From BANDS connector on Main
25T T37-1 13"
JULY 30th 2024 VK3PE ADDED SOME NOTES
ADDRESS SELECT
21T T37-0 11"
30m
17/15m
Solder JP10 and JP11 closed if using V012 LPF boards
160m
7T T37-0 4"
10T T37-2 6"
40m
26T T37-1 14"
20T T37-10 11"
